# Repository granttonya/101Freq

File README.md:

# 101Freq
Yaesu FT-101 Frequency Counter And Display

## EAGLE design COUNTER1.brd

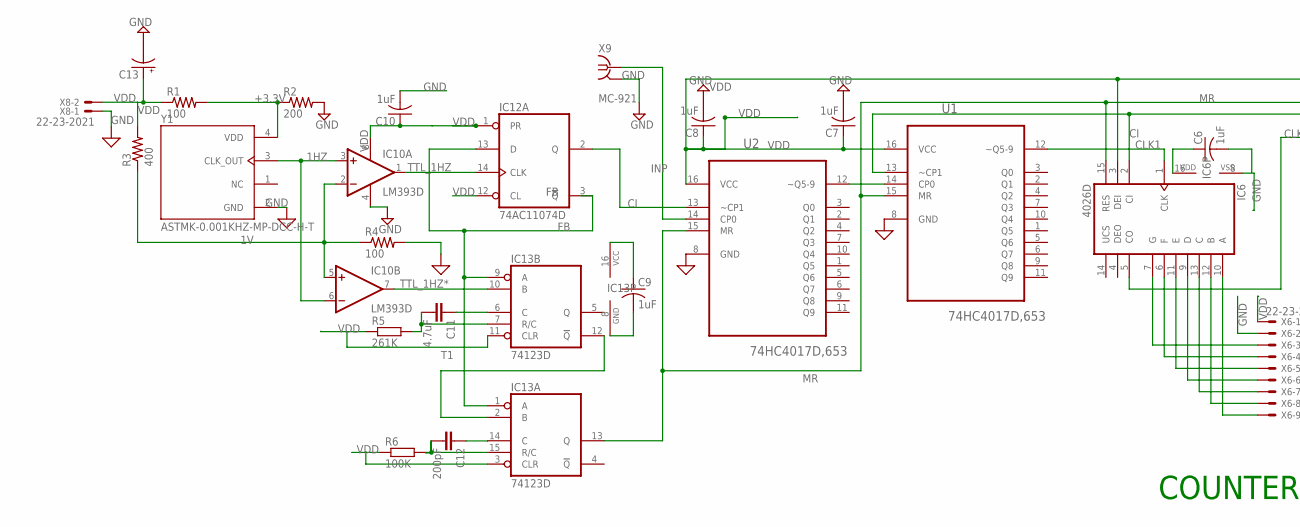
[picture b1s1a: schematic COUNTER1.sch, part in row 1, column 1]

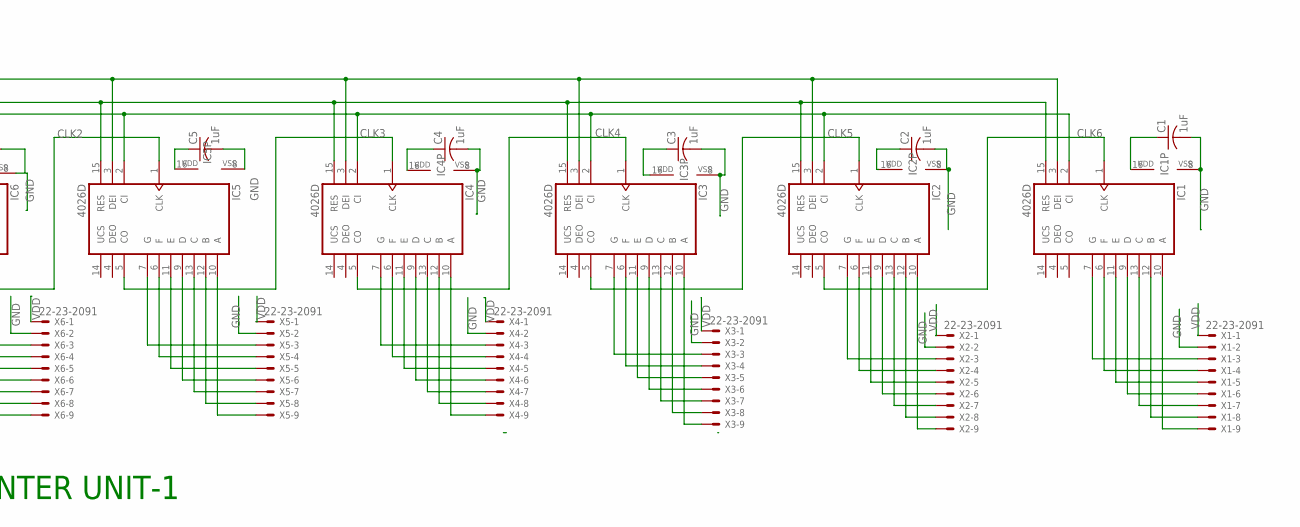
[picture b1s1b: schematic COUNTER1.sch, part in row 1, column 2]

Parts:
C1, C2, C3, C4, C5, C6, C7, C8, C9, C10: 1uF; C0603
C11: 4.7uF; C0603
C12: 200pF; C0603
C13: CPOL-USE2-5; E2-5
IC1, IC2, IC3, IC4, IC5, IC6: 4026D; SO16
IC10: LM393D; SO08
IC12: 74AC11074D; SO14
IC13: 74123D; SO16
R1, R4: 100; R0603
R2: 200; R0603
R3: 400; R0603
R5: 261K; R0603
R6: 100K; R0603
U1, U2: 74HC4017D,653; SOIC127P600X175-16N
X1, X2, X3, X4, X5, X6: 22-23-2091
X8: 22-23-2021
X9: MC-921
Y1: ASTMK-0.001KHZ-MP-DCC-H-T; OSC_ASTMK-0.001KHZ-MP-DCC-H-T

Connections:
1HZ: IC10.3 (+IN), IC10.6 (-IN), Y1.3 (CLK_OUT)
1V: IC10.2 (-IN), IC10.5 (+IN), R3.1, R4.1
+3.3V: R1.2, R2.1, Y1.4 (VDD)
CI: IC1.2 (CI), IC2.2 (CI), IC3.2 (CI), IC4.2 (CI), IC5.2 (CI), IC6.2 (CI), IC12.2 (Q), U1.13 (~CP1), U2.13 (~CP1)
CLK1: IC6.1 (CLK), U1.12 (~Q5-9)
CLK2: IC5.1 (CLK), IC6.5 (CO)
CLK3: IC4.1 (CLK), IC5.5 (CO)
CLK4: IC3.1 (CLK), IC4.5 (CO)
CLK5: IC2.1 (CLK), IC3.5 (CO)
CLK6: IC1.1 (CLK), IC2.5 (CO)
FB: IC12.3 (!Q), IC12.13 (D), IC13.1 (A), IC13.9 (A)
GND: C1.2, C2.2, C3.2, C4.2, C5.2, C6.2, C7.2, C8.2, C9.2, C10.2, C13.-, IC1.8 (VSS), IC2.8 (VSS), IC3.8 (VSS), IC4.8 (VSS), IC5.8 (VSS), IC6.8 (VSS), IC10.4 (V-), IC12.4 (GND), IC13.8 (GND), R2.2, R4.2, U1.8 (GND), U2.8 (GND), X1.2, X2.2, X3.2, X4.2, X5.2, X6.2, X8.1, X9.2@1 (GND), X9.2@2 (GND), Y1.2 (GND)
INP: U2.14 (CP0), X9.1
MR: IC1.15 (RES), IC2.15 (RES), IC3.15 (RES), IC4.15 (RES), IC5.15 (RES), IC6.15 (RES), IC13.13 (Q), U1.15 (MR), U2.15 (MR)
unnamed: C11.1, IC13.6 (C)
unnamed: IC1.10 (A), X1.9
unnamed: IC1.12 (B), X1.8
unnamed: IC1.13 (C), X1.7
unnamed: IC1.9 (D), X1.6
unnamed: IC1.11 (E), X1.5
unnamed: IC1.6 (F), X1.4
unnamed: IC1.7 (G), X1.3
unnamed: IC2.10 (A), X2.9
unnamed: IC2.12 (B), X2.8
unnamed: IC2.13 (C), X2.7
unnamed: IC2.9 (D), X2.6
unnamed: IC2.11 (E), X2.5
unnamed: IC2.6 (F), X2.4
unnamed: IC2.7 (G), X2.3
unnamed: IC3.10 (A), X3.9
unnamed: IC3.12 (B), X3.8
unnamed: IC3.13 (C), X3.7
unnamed: IC3.9 (D), X3.6
unnamed: IC3.11 (E), X3.5
unnamed: IC3.6 (F), X3.4
unnamed: IC3.7 (G), X3.3
unnamed: IC6.12 (B), X6.8
unnamed: IC4.10 (A), X4.9
unnamed: IC4.12 (B), X4.8
unnamed: IC4.13 (C), X4.7
unnamed: IC4.9 (D), X4.6
unnamed: IC4.11 (E), X4.5
unnamed: IC4.6 (F), X4.4
unnamed: IC4.7 (G), X4.3
unnamed: IC5.10 (A), X5.9
unnamed: IC5.12 (B), X5.8
unnamed: IC5.13 (C), X5.7
unnamed: IC5.9 (D), X5.6
unnamed: IC5.11 (E), X5.5
unnamed: IC5.6 (F), X5.4
unnamed: IC5.7 (G), X5.3
unnamed: IC6.10 (A), X6.9
unnamed: IC6.13 (C), X6.7
unnamed: IC6.9 (D), X6.6
unnamed: IC6.11 (E), X6.5
unnamed: IC6.6 (F), X6.4
unnamed: IC6.7 (G), X6.3
unnamed: C12.1, IC13.14 (C)
unnamed: U1.14 (CP0), U2.12 (~Q5-9)
RC1: C11.2, IC13.7 (R/C), R5.2
RC2: C12.2, IC13.15 (R/C), R6.2
T1: IC13.2 (B), IC13.12 (!Q)
TTL_1HZ: IC10.1 (OUT), IC12.14 (CLK)
TTL_1HZ*: IC10.7 (OUT), IC13.10 (B)
VDD: C1.1, C2.1, C3.1, C4.1, C5.1, C6.1, C7.1, C8.1, C9.1, C10.1, C13.+, IC1.3 (DEI), IC1.16 (VDD), IC2.3 (DEI), IC2.16 (VDD), IC3.3 (DEI), IC3.16 (VDD), IC4.3 (DEI), IC4.16 (VDD), IC5.3 (DEI), IC5.16 (VDD), IC6.3 (DEI), IC6.16 (VDD), IC10.8 (V+), IC12.1 (PR), IC12.11 (VCC), IC12.12 (CL), IC13.3 (CLR), IC13.16 (VCC), R1.1, R3.2, R5.1, R6.1, U1.16 (VCC), U2.16 (VCC), X1.1, X2.1, X3.1, X4.1, X5.1, X6.1, X8.2

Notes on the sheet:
COUNTER UNIT-1

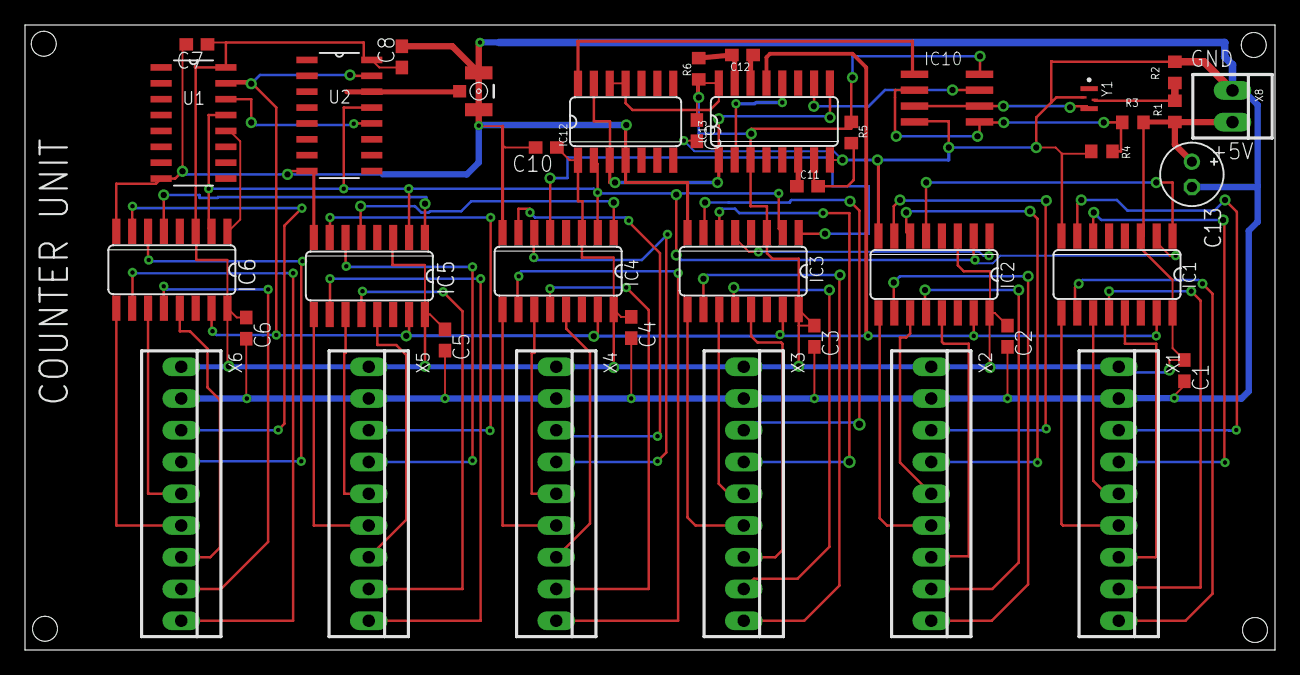
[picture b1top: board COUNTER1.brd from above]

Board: 2 copper layers, 100.0 x 50.0 mm, 39 parts (0 on the bottom side), 65 nets.

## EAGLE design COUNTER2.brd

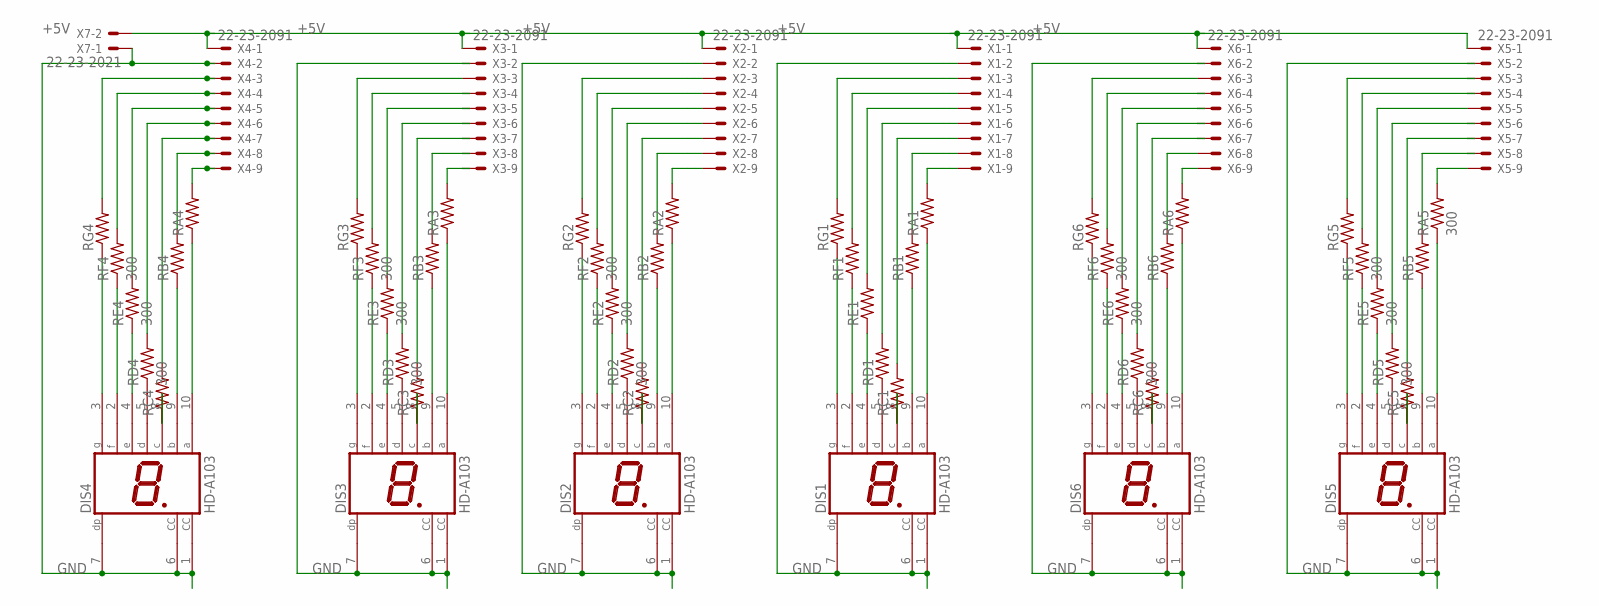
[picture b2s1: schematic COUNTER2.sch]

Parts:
DIS1, DIS2, DIS3, DIS4, DIS5, DIS6: HD-A103; HDSP-A
RA1, RA2, RA3, RA4, RA6: R-US_R0805; R0805
RA5: 300; R0805
RB1, RB2, RB3, RB4, RB5, RB6: R-US_R0805; R0805
RC1, RC2, RC3, RC4, RC5, RC6: R-US_R0805; R0805
RD1: R-US_0204/5; 0204/5
RD2, RD3, RD4, RD5, RD6: 300; 0204/5
RE1: R-US_0204/5; 0204/5
RE2, RE3, RE4, RE5, RE6: 300; 0204/5
RF1: R-US_0204/5; 0204/5
RF2, RF3, RF4, RF5, RF6: 300; 0204/5
RG1, RG2, RG3, RG4, RG5, RG6: R-US_0204/5; 0204/5
X1, X2, X3, X4, X5, X6: 22-23-2091
X7: 22-23-2021

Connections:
+5V: X1.1, X2.1, X3.1, X4.1, X5.1, X6.1, X7.2
GND: DIS1.1 (CC), DIS1.6 (CC), DIS1.7 (DP), DIS2.1 (CC), DIS2.6 (CC), DIS2.7 (DP), DIS3.1 (CC), DIS3.6 (CC), DIS3.7 (DP), DIS4.1 (CC), DIS4.6 (CC), DIS4.7 (DP), DIS5.1 (CC), DIS5.6 (CC), DIS5.7 (DP), DIS6.1 (CC), DIS6.6 (CC), DIS6.7 (DP), X1.2, X2.2, X3.2, X4.2, X5.2, X6.2, X7.1
unnamed: RA1.2, X1.9
unnamed: DIS2.10 (A), RA2.1
unnamed: RB2.2, X2.8
unnamed: DIS2.9 (B), RB2.1
unnamed: RC2.2, X2.7
unnamed: DIS2.8 (C), RC2.1
unnamed: RD2.2, X2.6
unnamed: DIS2.5 (D), RD2.1
unnamed: RE2.2, X2.5
unnamed: DIS2.4 (E), RE2.1
unnamed: RF2.2, X2.4
unnamed: DIS2.2 (F), RF2.1
unnamed: RG2.2, X2.3
unnamed: DIS2.3 (G), RG2.1
unnamed: RA2.2, X2.9
unnamed: DIS3.10 (A), RA3.1
unnamed: RB3.2, X3.8
unnamed: DIS3.9 (B), RB3.1
unnamed: RC3.2, X3.7
unnamed: DIS3.8 (C), RC3.1
unnamed: RD3.2, X3.6
unnamed: DIS3.5 (D), RD3.1
unnamed: RE3.2, X3.5
unnamed: DIS3.4 (E), RE3.1
unnamed: RF3.2, X3.4
unnamed: DIS3.2 (F), RF3.1
unnamed: DIS3.3 (G), RG3.1
unnamed: RA3.2, X3.9
unnamed: DIS4.10 (A), RA4.1
unnamed: RB4.2, X4.8
unnamed: DIS4.9 (B), RB4.1
unnamed: RC4.2, X4.7
unnamed: DIS4.8 (C), RC4.1
unnamed: RD4.2, X4.6
unnamed: DIS4.5 (D), RD4.1
unnamed: RE4.2, X4.5
unnamed: DIS4.4 (E), RE4.1
unnamed: RF4.2, X4.4
unnamed: DIS4.2 (F), RF4.1
unnamed: RG4.2, X4.3
unnamed: DIS4.3 (G), RG4.1
unnamed: RA4.2, X4.9
unnamed: DIS5.10 (A), RA5.1
unnamed: RB5.2, X5.8
unnamed: DIS5.9 (B), RB5.1
unnamed: RC5.2, X5.7
unnamed: DIS5.8 (C), RC5.1
unnamed: RD5.2, X5.6
unnamed: DIS5.5 (D), RD5.1
unnamed: RE5.2, X5.5
unnamed: DIS5.4 (E), RE5.1
unnamed: RF5.2, X5.4
unnamed: DIS5.2 (F), RF5.1
unnamed: RG5.2, X5.3
unnamed: DIS5.3 (G), RG5.1
unnamed: RA5.2, X5.9
unnamed: DIS6.10 (A), RA6.1
unnamed: RB6.2, X6.8
unnamed: DIS6.9 (B), RB6.1
unnamed: RC6.2, X6.7
unnamed: DIS6.8 (C), RC6.1
unnamed: RD6.2, X6.6
unnamed: DIS6.5 (D), RD6.1
unnamed: RE6.2, X6.5
unnamed: DIS6.4 (E), RE6.1
unnamed: RF6.2, X6.4
unnamed: DIS6.2 (F), RF6.1
unnamed: RG6.2, X6.3
unnamed: DIS6.3 (G), RG6.1
unnamed: RA6.2, X6.9
unnamed: RG3.2, X3.3
unnamed: DIS1.10 (A), RA1.1
unnamed: RB1.2, X1.8
unnamed: DIS1.9 (B), RB1.1
unnamed: RC1.2, X1.7
unnamed: DIS1.8 (C), RC1.1
unnamed: RD1.2, X1.6
unnamed: DIS1.5 (D), RD1.1
unnamed: RE1.2, X1.5
unnamed: DIS1.4 (E), RE1.1
unnamed: RF1.2, X1.4
unnamed: DIS1.2 (F), RF1.1
unnamed: RG1.2, X1.3
unnamed: DIS1.3 (G), RG1.1

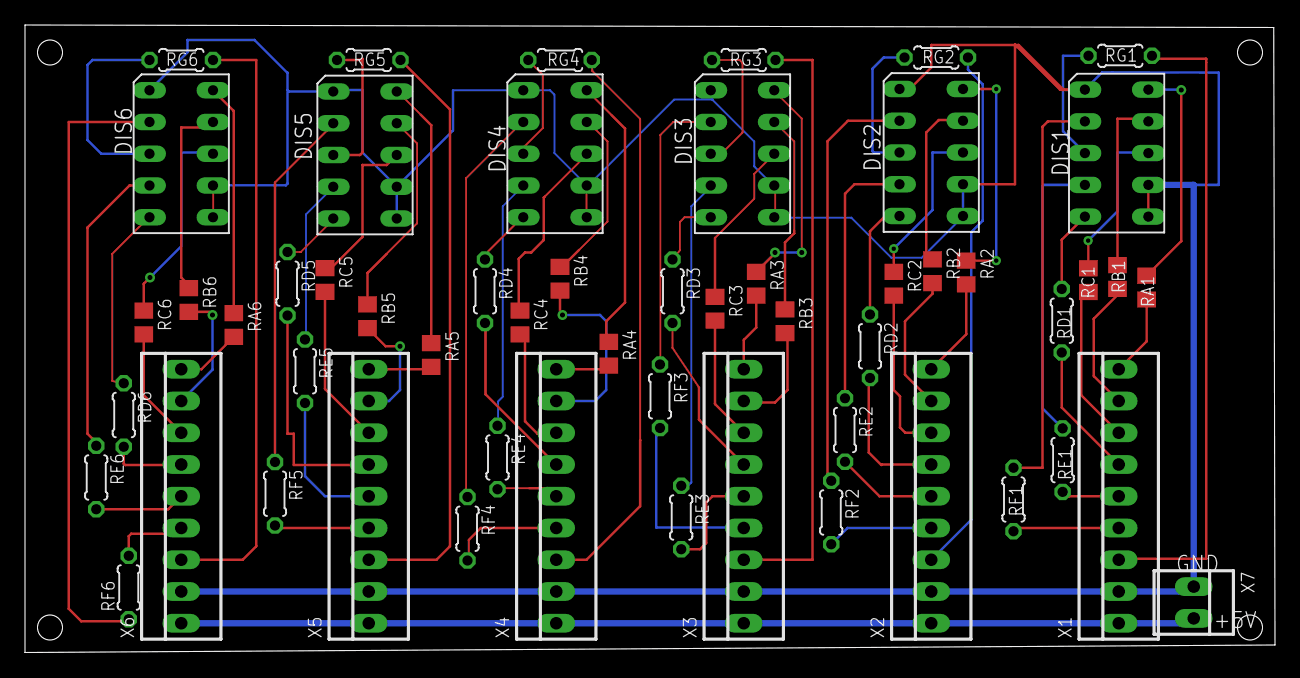
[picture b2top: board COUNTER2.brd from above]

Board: 2 copper layers, 100.0 x 50.2 mm, 55 parts (0 on the bottom side), 86 nets.

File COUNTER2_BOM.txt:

Partlist exported from D:/1PROJECTS/1UPWORK/Counter/DESIGN/COUNTER2.sch at 12/04/2021 21:41

Part Value      Device      Package    Description                          MF    MPN        OC_FARNELL OC_NEWARK POPULARITY
DIS1 HD-A103    HD-A103     HDSP-A     LED DISPLAY                                           unknown    unknown   0         
DIS2 HD-A103    HD-A103     HDSP-A     LED DISPLAY                                           unknown    unknown   0         
DIS3 HD-A103    HD-A103     HDSP-A     LED DISPLAY                                           unknown    unknown   0         
DIS4 HD-A103    HD-A103     HDSP-A     LED DISPLAY                                           unknown    unknown   0         
DIS5 HD-A103    HD-A103     HDSP-A     LED DISPLAY                                           unknown    unknown   0         
DIS6 HD-A103    HD-A103     HDSP-A     LED DISPLAY                                           unknown    unknown   0         
RA1             R-US_R0805  R0805      RESISTOR, American symbol                                                            
RA2             R-US_R0805  R0805      RESISTOR, American symbol                                                            
RA3             R-US_R0805  R0805      RESISTOR, American symbol                                                            
RA4             R-US_R0805  R0805      RESISTOR, American symbol                                                            
RA5  300        R-US_R0805  R0805      RESISTOR, American symbol                                                            
RA6             R-US_R0805  R0805      RESISTOR, American symbol                                                            
RB1             R-US_R0805  R0805      RESISTOR, American symbol                                                            
RB2             R-US_R0805  R0805      RESISTOR, American symbol                                                            
RB3             R-US_R0805  R0805      RESISTOR, American symbol                                                            
RB4             R-US_R0805  R0805      RESISTOR, American symbol                                                            
RB5             R-US_R0805  R0805      RESISTOR, American symbol                                                            
RB6             R-US_R0805  R0805      RESISTOR, American symbol                                                            
RC1             R-US_R0805  R0805      RESISTOR, American symbol                                                            
RC2             R-US_R0805  R0805      RESISTOR, American symbol                                                            
RC3             R-US_R0805  R0805      RESISTOR, American symbol                                                            
RC4             R-US_R0805  R0805      RESISTOR, American symbol                                                            
RC5             R-US_R0805  R0805      RESISTOR, American symbol                                                            
RC6             R-US_R0805  R0805      RESISTOR, American symbol                                                            
RD1             R-US_0204/5 0204/5     RESISTOR, American symbol                                                            
RD2  300        R-US_0204/5 0204/5     RESISTOR, American symbol                                                            
RD3  300        R-US_0204/5 0204/5     RESISTOR, American symbol                                                            
RD4  300        R-US_0204/5 0204/5     RESISTOR, American symbol                                                            
RD5  300        R-US_0204/5 0204/5     RESISTOR, American symbol                                                            
RD6  300        R-US_0204/5 0204/5     RESISTOR, American symbol                                                            
RE1             R-US_0204/5 0204/5     RESISTOR, American symbol                                                            
RE2  300        R-US_0204/5 0204/5     RESISTOR, American symbol                                                            
RE3  300        R-US_0204/5 0204/5     RESISTOR, American symbol                                                            
RE4  300        R-US_0204/5 0204/5     RESISTOR, American symbol                                                            
RE5  300        R-US_0204/5 0204/5     RESISTOR, American symbol                                                            
RE6  300        R-US_0204/5 0204/5     RESISTOR, American symbol                                                            
RF1             R-US_0204/5 0204/5     RESISTOR, American symbol                                                            
RF2  300        R-US_0204/5 0204/5     RESISTOR, American symbol                                                            
RF3  300        R-US_0204/5 0204/5     RESISTOR, American symbol                                                            
RF4  300        R-US_0204/5 0204/5     RESISTOR, American symbol                                                            
RF5  300        R-US_0204/5 0204/5     RESISTOR, American symbol                                                            
RF6  300        R-US_0204/5 0204/5     RESISTOR, American symbol                                                            
RG1             R-US_0204/5 0204/5     RESISTOR, American symbol                                                            
RG2             R-US_0204/5 0204/5     RESISTOR, American symbol                                                            
RG3             R-US_0204/5 0204/5     RESISTOR, American symbol                                                            
RG4             R-US_0204/5 0204/5     RESISTOR, American symbol                                                            
RG5             R-US_0204/5 0204/5     RESISTOR, American symbol                                                            
RG6             R-US_0204/5 0204/5     RESISTOR, American symbol                                                            
X1   22-23-2091 22-23-2091  22-23-2091 .100" (2.54mm) Center Header - 9 Pin MOLEX 22-23-2091 1756827    56H0450   1         
X2   22-23-2091 22-23-2091  22-23-2091 .100" (2.54mm) Center Header - 9 Pin MOLEX 22-23-2091 1756827    56H0450   1         
X3   22-23-2091 22-23-2091  22-23-2091 .100" (2.54mm) Center Header - 9 Pin MOLEX 22-23-2091 1756827    56H0450   1         
X4   22-23-2091 22-23-2091  22-23-2091 .100" (2.54mm) Center Header - 9 Pin MOLEX 22-23-2091 1756827    56H0450   1         
X5   22-23-2091 22-23-2091  22-23-2091 .100" (2.54mm) Center Header - 9 Pin MOLEX 22-23-2091 1756827    56H0450   1         
X6   22-23-2091 22-23-2091  22-23-2091 .100" (2.54mm) Center Header - 9 Pin MOLEX 22-23-2091 1756827    56H0450   1         
X7   22-23-2021 22-23-2021  22-23-2021 .100" (2.54mm) Center Header - 2 Pin MOLEX 22-23-2021 1462926    25C3832   40

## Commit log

2021-06-03 Added File
